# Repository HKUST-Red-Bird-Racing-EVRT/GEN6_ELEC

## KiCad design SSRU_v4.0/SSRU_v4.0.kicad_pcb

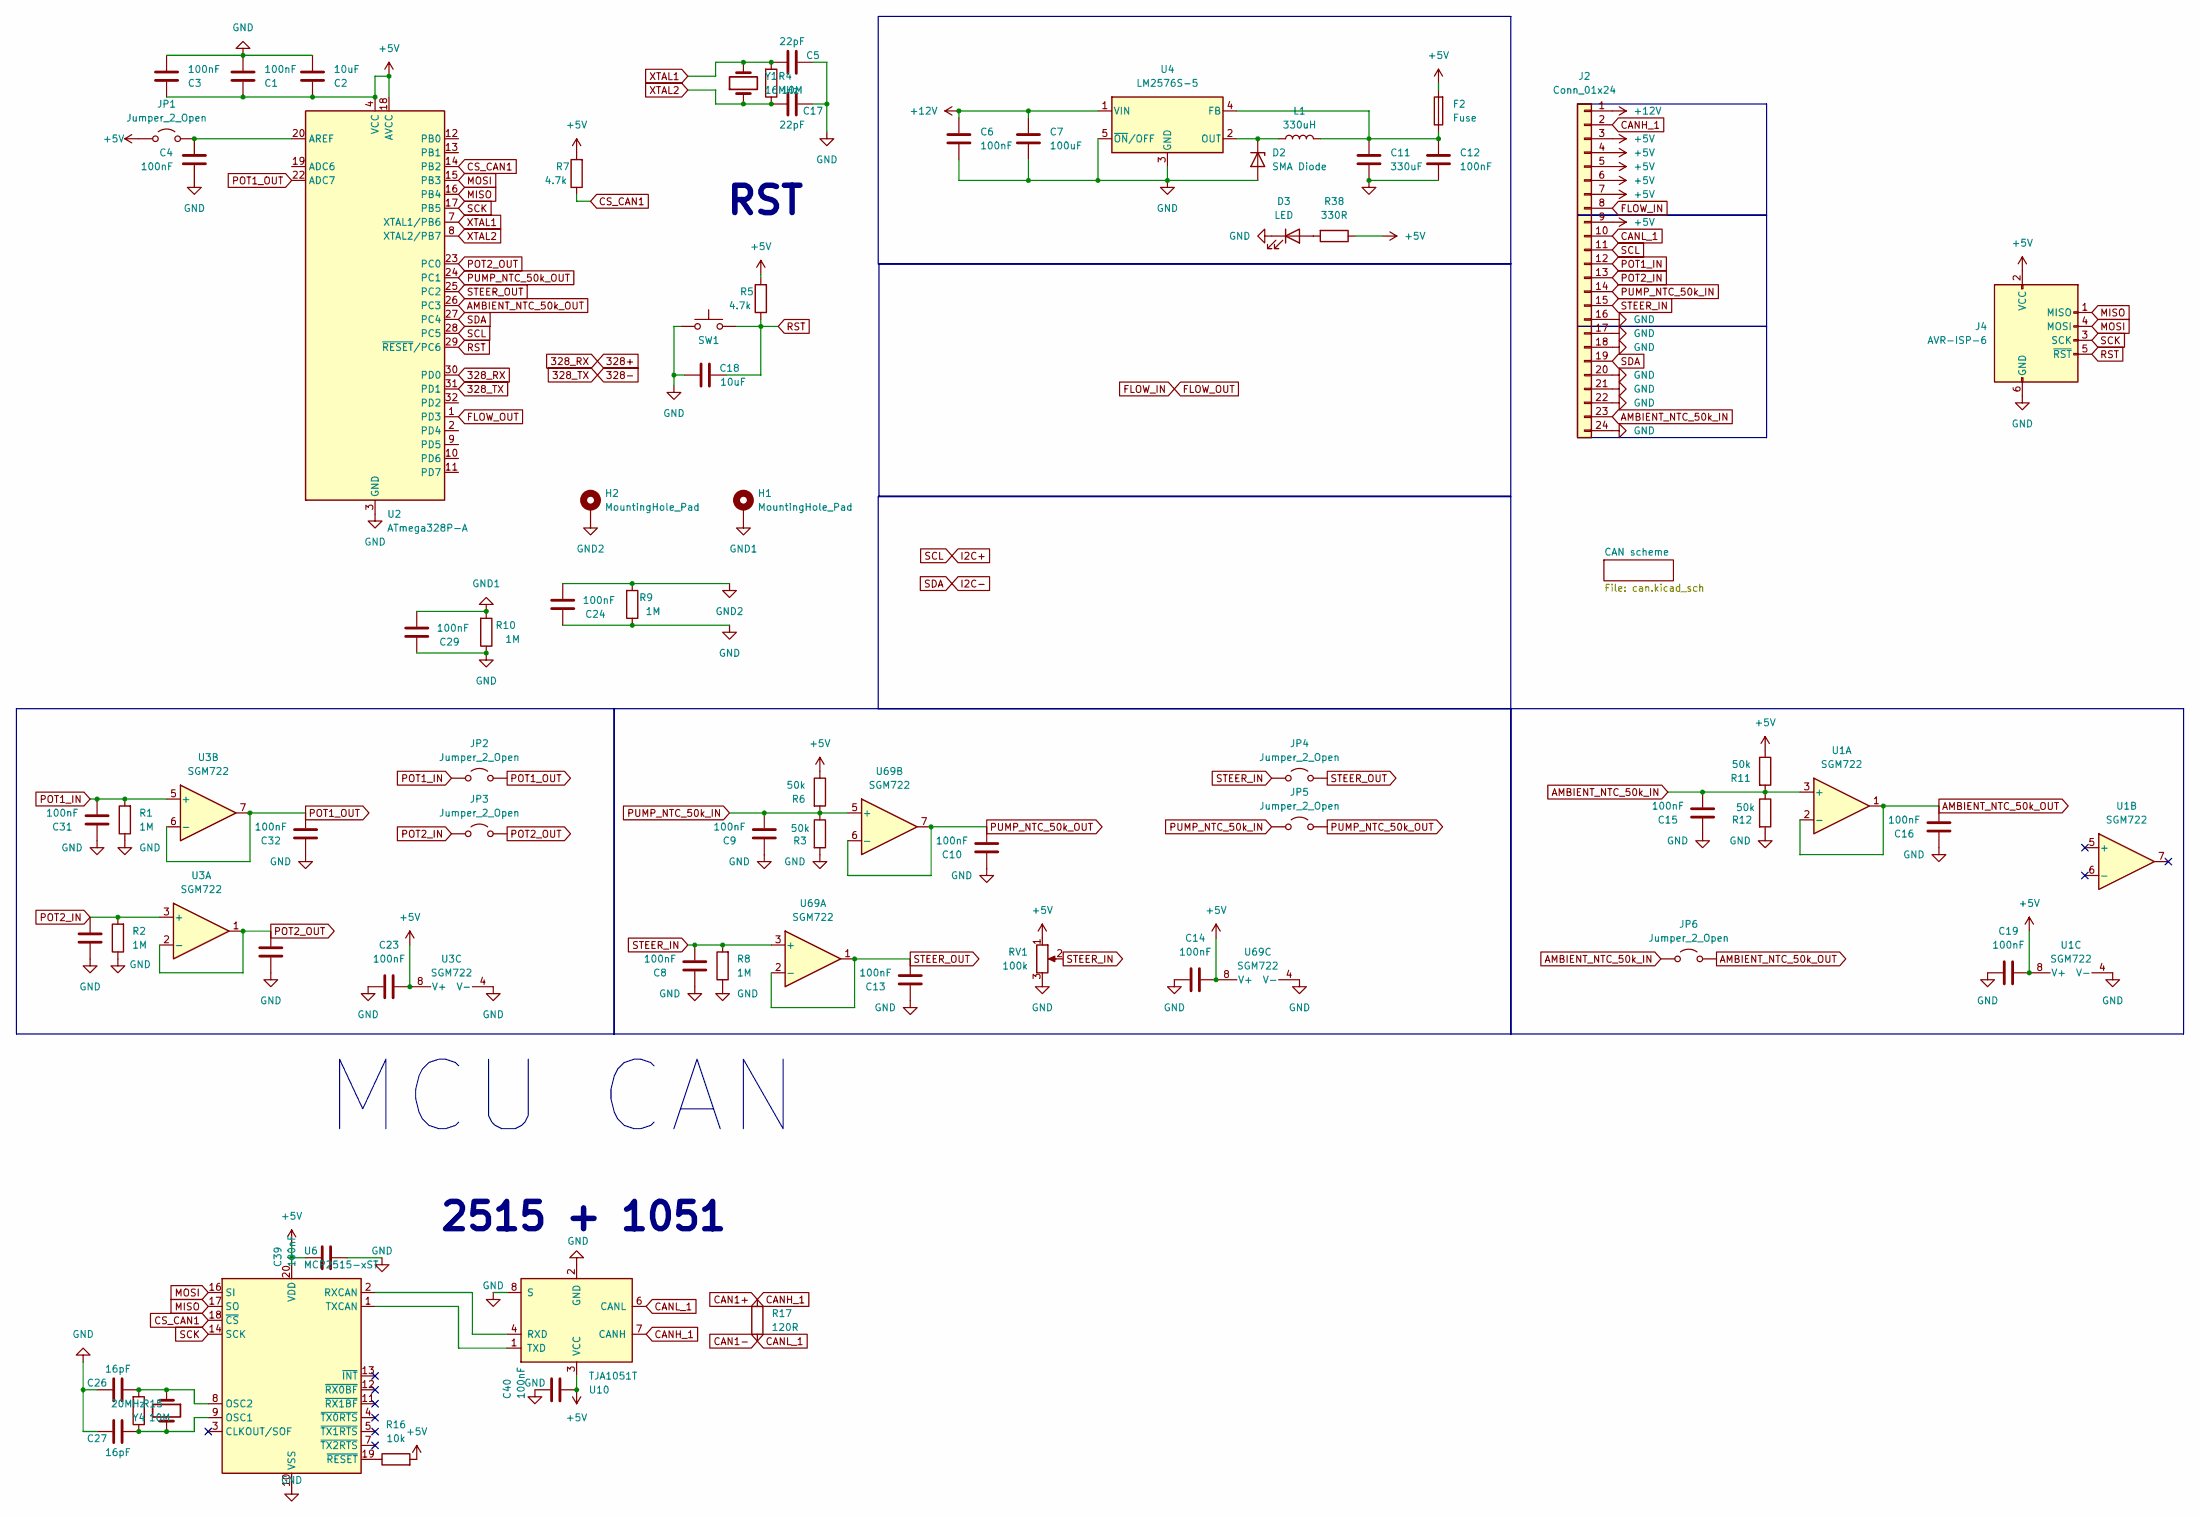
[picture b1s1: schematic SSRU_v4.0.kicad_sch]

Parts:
C1, C3, C4, C6, C8, C9, C10, C12, C13, C14, C15, C16, C19, C23, C24, C29, C31, C32, C36, C37, C39, C40: 100nF; C_0805_2012Metric_Pad1.18x1.45mm_HandSolder_L
C2, C18: 10uF; C_0805_2012Metric_Pad1.18x1.45mm_HandSolder_L
C5, C17: 22pF; C_0805_2012Metric_Pad1.18x1.45mm_HandSolder_L
C7: 100uF; CP_Radial_D6.3mm_P2.50mm_handsolder
C11: 330uF; CP_Radial_D6.3mm_P2.50mm_handsolder
C26, C27: 16pF; C_0805_2012Metric_Pad1.18x1.45mm_HandSolder_L
D2: SMA Diode; D_SMA_Handsoldering
D3: LED; LED_0805_2012Metric_Pad1.45x1.40mm_HandSolder
F2: Fuse; Fuse_1210_3225Metric_Pad1.42x2.65mm_HandSolder
H1, H2: MountingHole_Pad; MountingHole_3.2mm_M3_ISO14580_Pad
J2: Conn_01x24; HD241_24pin
J4: AVR-ISP-6; PinHeader_2x03_P2.54mm_Vertical
JP1, JP2, JP3, JP4, JP5, JP6: Jumper_2_Open; SolderJumper-2_P1.3mm_Open_Pad1.0x1.5mm
L1: 330uH; L_10.4x10.4_H4.8
R1, R2, R8, R9, R10: 1M; R_0805_2012Metric_Pad1.20x1.40mm_HandSolder_L
R3, R6, R11, R12: 50k; R_0805_2012Metric_Pad1.20x1.40mm_HandSolder_L
R4, R15: 10M; R_0805_2012Metric_Pad1.20x1.40mm_HandSolder_L
R5, R7: 4.7k; R_0805_2012Metric_Pad1.20x1.40mm_HandSolder_L
R16: 10k; R_0805_2012Metric_Pad1.20x1.40mm_HandSolder_L
R17: 120R; R_0805_2012Metric_Pad1.20x1.40mm_HandSolder_L
R38: 330R; R_0805_2012Metric_Pad1.20x1.40mm_HandSolder_L
RV1: 100k
SW1: SW_Push; SW_PUSH_6mm_H5mm
U1, U3, U69: SGM722; SOIC-8_3.9x4.9mm_P1.27mm_RMC_Handsolder
U2: ATmega328P-A; TQFP-32_7x7mm_P0.8mm_L
U4: LM2576S-5; TO-263-5_TabPin3_Handsolder
U6: MCP2515-xST; TSSOP-20_4.4x6.5mm_P0.65mm
U10: TJA1051T; SOIC-8_3.9x4.9mm_P1.27mm_RMC_Handsolder
Y1: 16MHz; Crystal_HC49-U_Vertical_W_SMD
Y4: 20MHz; Crystal_HC49-U_Vertical_W_SMD

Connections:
328+: U2.30 (PD0)
328-: U2.31 (PD1)
+5V: C1.2, C2.2, C3.2, C14.2, C19.2, C23.2, C39.2, C40.1, F2.2, J2.3, J2.4, J2.5, J2.6, J2.7, J2.9, J4.2 (VCC), JP1.1 (A), R5.2, R6.1, R7.2, R11.1, R16.2, R38.1, RV1.1, U1.8 (V+), U2.4 (VCC), U2.6 (VCC), U2.18 (AVCC), U3.8 (V+), U6.20 (VDD), U10.3 (VCC), U69.8 (V+)
+12V: C6.2, C7.1, J2.1, U4.1 (VIN)
AMBIENT_NTC_50k_IN: C15.2, J2.23, JP6.1 (A), R11.2, R12.1, U1.3 (+)
AMBIENT_NTC_50k_OUT: C16.2, JP6.2 (B), U1.1, U1.2 (-), U2.26 (PC3)
CAN1+: J2.2, R17.2, U10.7 (CANH)
CAN1-: J2.10, R17.1, U10.6 (CANL)
CS_CAN1: R7.1, U2.14 (PB2), U6.18 (~CS)
FLOW_IN: J2.8, U2.1 (PD3)
GND: C1.1, C2.1, C3.1, C4.1, C5.1, C6.1, C7.2, C8.1, C9.1, C10.1, C11.2, C12.1, C13.1, C14.1, C15.1, C16.1, C17.1, C18.1, C19.1, C23.1, C24.1, C26.1, C27.1, C29.1, C31.1, C32.1, C36.1, C37.1, C39.1, C40.2, D2.2 (A), D3.1 (K), J2.16, J2.17, J2.18, J2.20, J2.21, J2.22, J2.24, J4.6 (GND), R1.1, R2.1, R3.2, R8.1, R9.1, R10.1, R12.2, RV1.3, SW1.1, U1.4 (V-), U2.3 (GND), U2.5 (GND), U2.21 (GND), U3.4 (V-), U4.3 (GND), U4.5 (~ON/OFF), U6.10 (VSS), U10.2 (GND), U10.8 (S), U69.4 (V-)
GND1: C29.2, H1.1, R10.2
GND2: C24.2, H2.1, R9.2
I2C+: J2.11, U2.28 (PC5)
I2C-: J2.19, U2.27 (PC4)
MISO: J4.1 (MISO), U2.16 (PB4), U6.17 (SO)
MOSI: J4.4 (MOSI), U2.15 (PB3), U6.16 (SI)
unnamed: D2.1 (K), L1.1, U4.2 (OUT)
unnamed: D3.2 (A), R38.2
unnamed: C4.2, JP1.2 (B), U2.20 (AREF)
unnamed: C11.1, C12.2, F2.1, L1.2, U4.4 (FB)
unnamed: C27.2, R15.1, U6.9 (OSC1), Y4.2
unnamed: C26.2, R15.2, U6.8 (OSC2), Y4.1
unnamed: R16.1, U6.19 (~RESET)
unnamed: U6.2 (RXCAN), U10.4 (RXD)
unnamed: U6.1 (TXCAN), U10.1 (TXD)
POT1_IN: C31.2, J2.12, JP2.1 (A), R1.2, U3.5 (+)
POT1_OUT: C32.2, JP2.2 (B), U2.22 (ADC7), U3.6 (-), U3.7
POT2_IN: C36.2, J2.13, JP3.1 (A), R2.2, U3.3 (+)
POT2_OUT: C37.2, JP3.2 (B), U2.23 (PC0), U3.1, U3.2 (-)
PUMP_NTC_50k_IN: C9.2, J2.14, JP5.1 (A), R3.1, R6.2, U69.5 (+)
PUMP_NTC_50k_OUT: C10.2, JP5.2 (B), U2.24 (PC1), U69.6 (-), U69.7
RST: C18.2, J4.5 (~RST), R5.1, SW1.2, U2.29 (~RESET/PC6)
SCK: J4.3 (SCK), U2.17 (PB5), U6.14 (SCK)
STEER_IN: C8.2, J2.15, JP4.1 (A), R8.2, RV1.2, U69.3 (+)
STEER_OUT: C13.2, JP4.2 (B), U2.25 (PC2), U69.1, U69.2 (-)
XTAL1: C5.2, R4.2, U2.7 (XTAL1/PB6), Y1.2
XTAL2: C17.2, R4.1, U2.8 (XTAL2/PB7), Y1.1

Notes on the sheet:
MCU CAN
2515 + 1051
RST

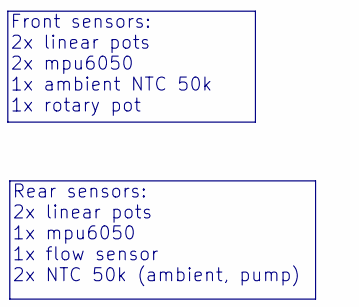
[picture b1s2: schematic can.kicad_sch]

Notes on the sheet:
Front sensors: 2x linear pots 2x mpu6050 1x ambient NTC 50k 1x rotary pot
Rear sensors: 2x linear pots 1x mpu6050 1x flow sensor 2x NTC 50k (ambient, pump)

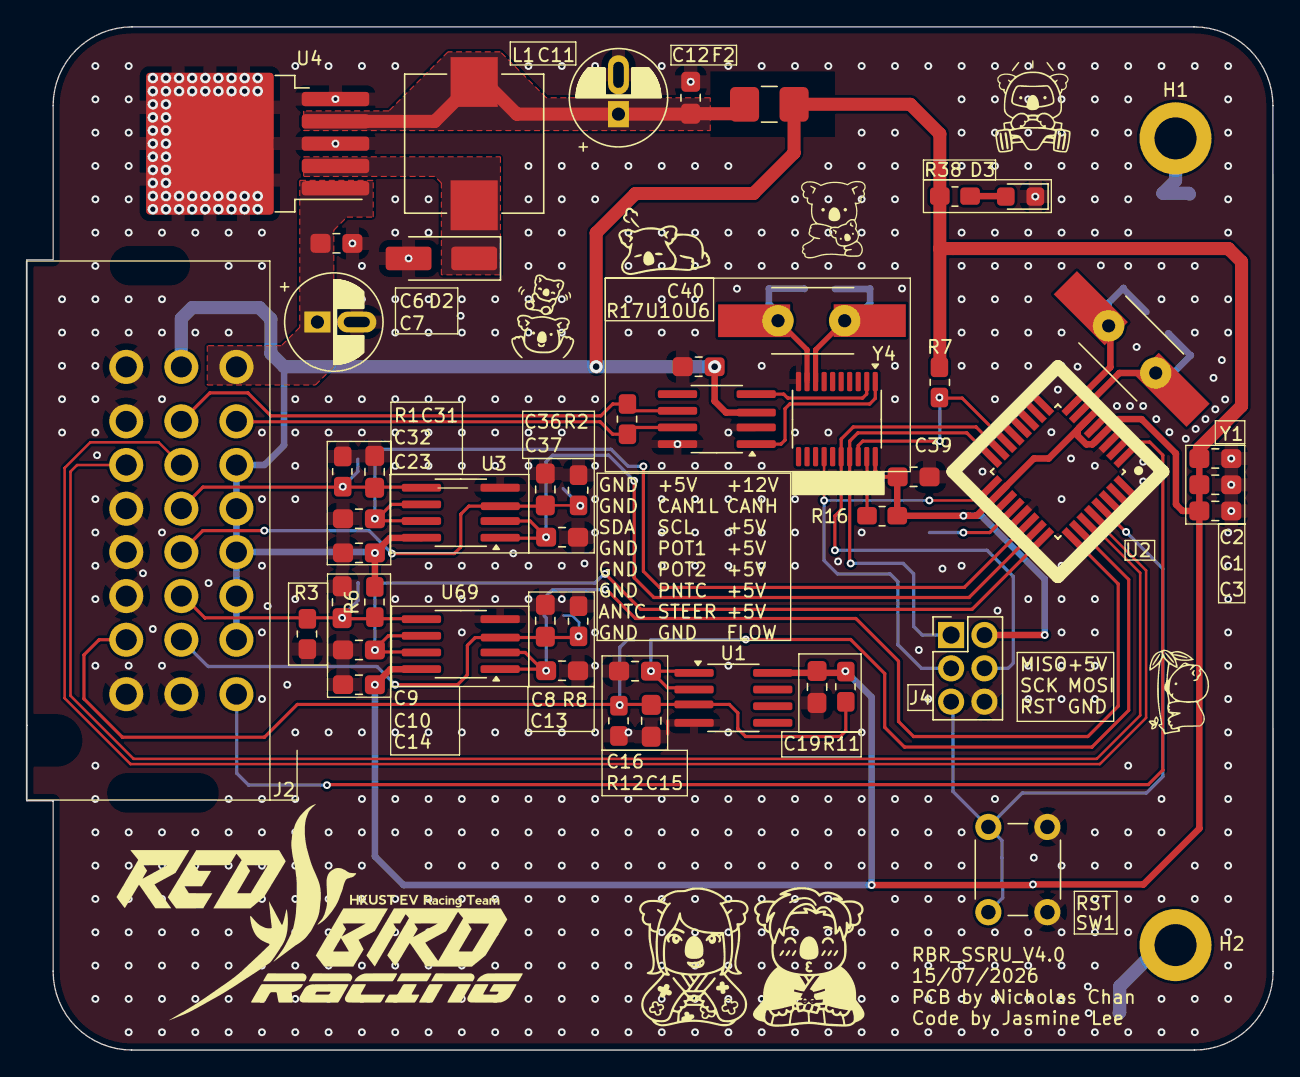
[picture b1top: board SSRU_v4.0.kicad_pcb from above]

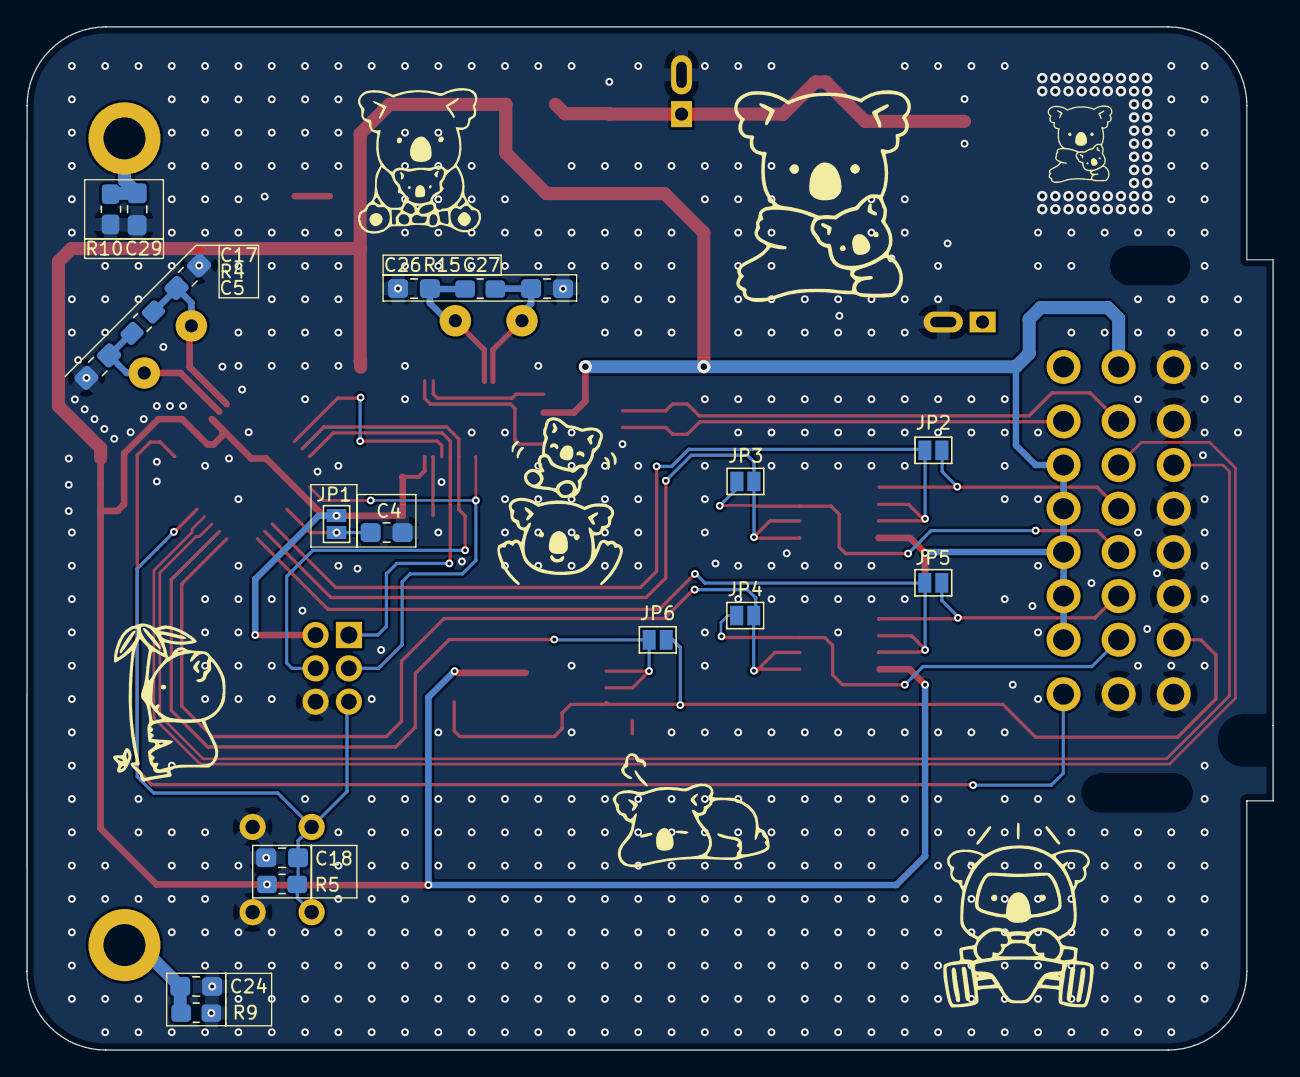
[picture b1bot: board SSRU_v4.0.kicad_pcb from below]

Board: 2 copper layers, 95.0 x 78.0 mm, 70 parts (19 on the bottom side), 36 nets.

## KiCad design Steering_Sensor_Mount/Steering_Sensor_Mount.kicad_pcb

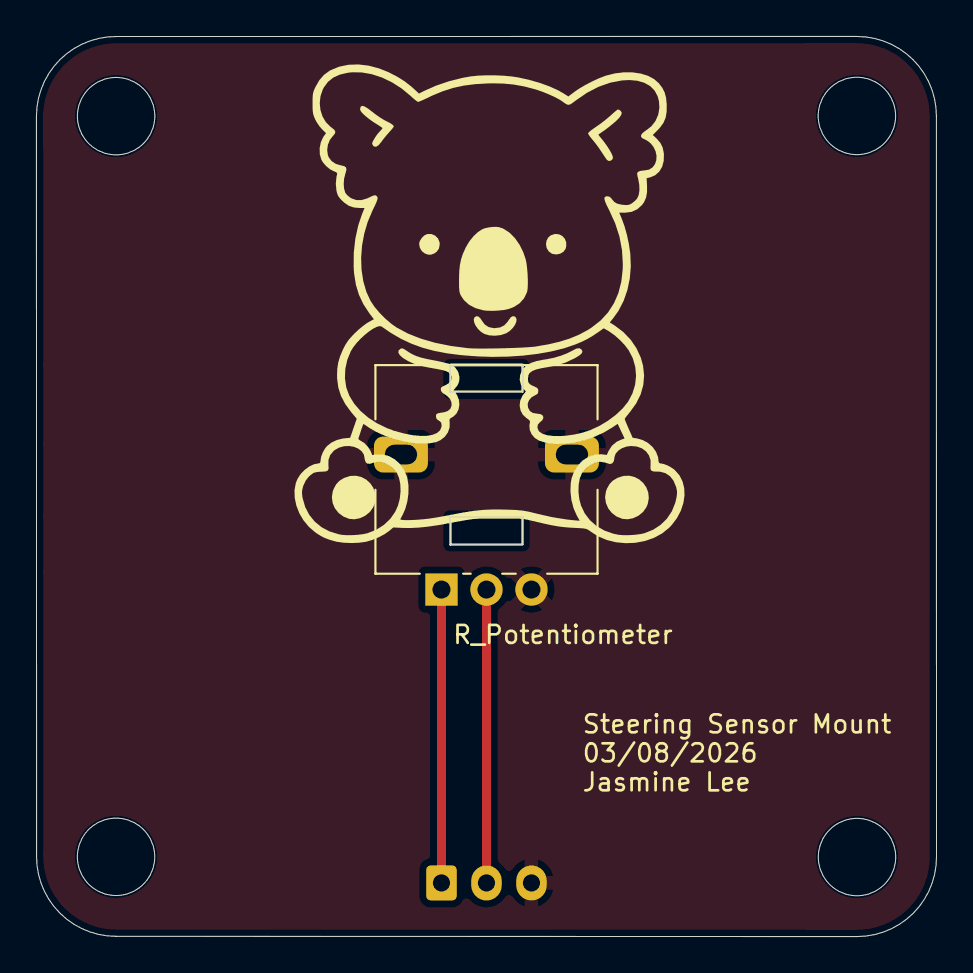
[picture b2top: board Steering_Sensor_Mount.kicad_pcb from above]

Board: 2 copper layers, 50.0 x 50.0 mm, 6 parts (1 on the bottom side), 3 nets.

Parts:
H1, H2, H3, H4: MountingHole; MountingHole_4.3mm_M4
J1: Conn_01x03; JST_XH_B3B-XH-A_1x03_P2.50mm_Vertical
RV1: R_Potentiometer; Potentiometer_Alps_RK09L_Single_Vertical

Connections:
+5V: J1.1, RV1.1
GND: J1.3, RV1.3, RV1.MP (MountPin)
unnamed: J1.2, RV1.2

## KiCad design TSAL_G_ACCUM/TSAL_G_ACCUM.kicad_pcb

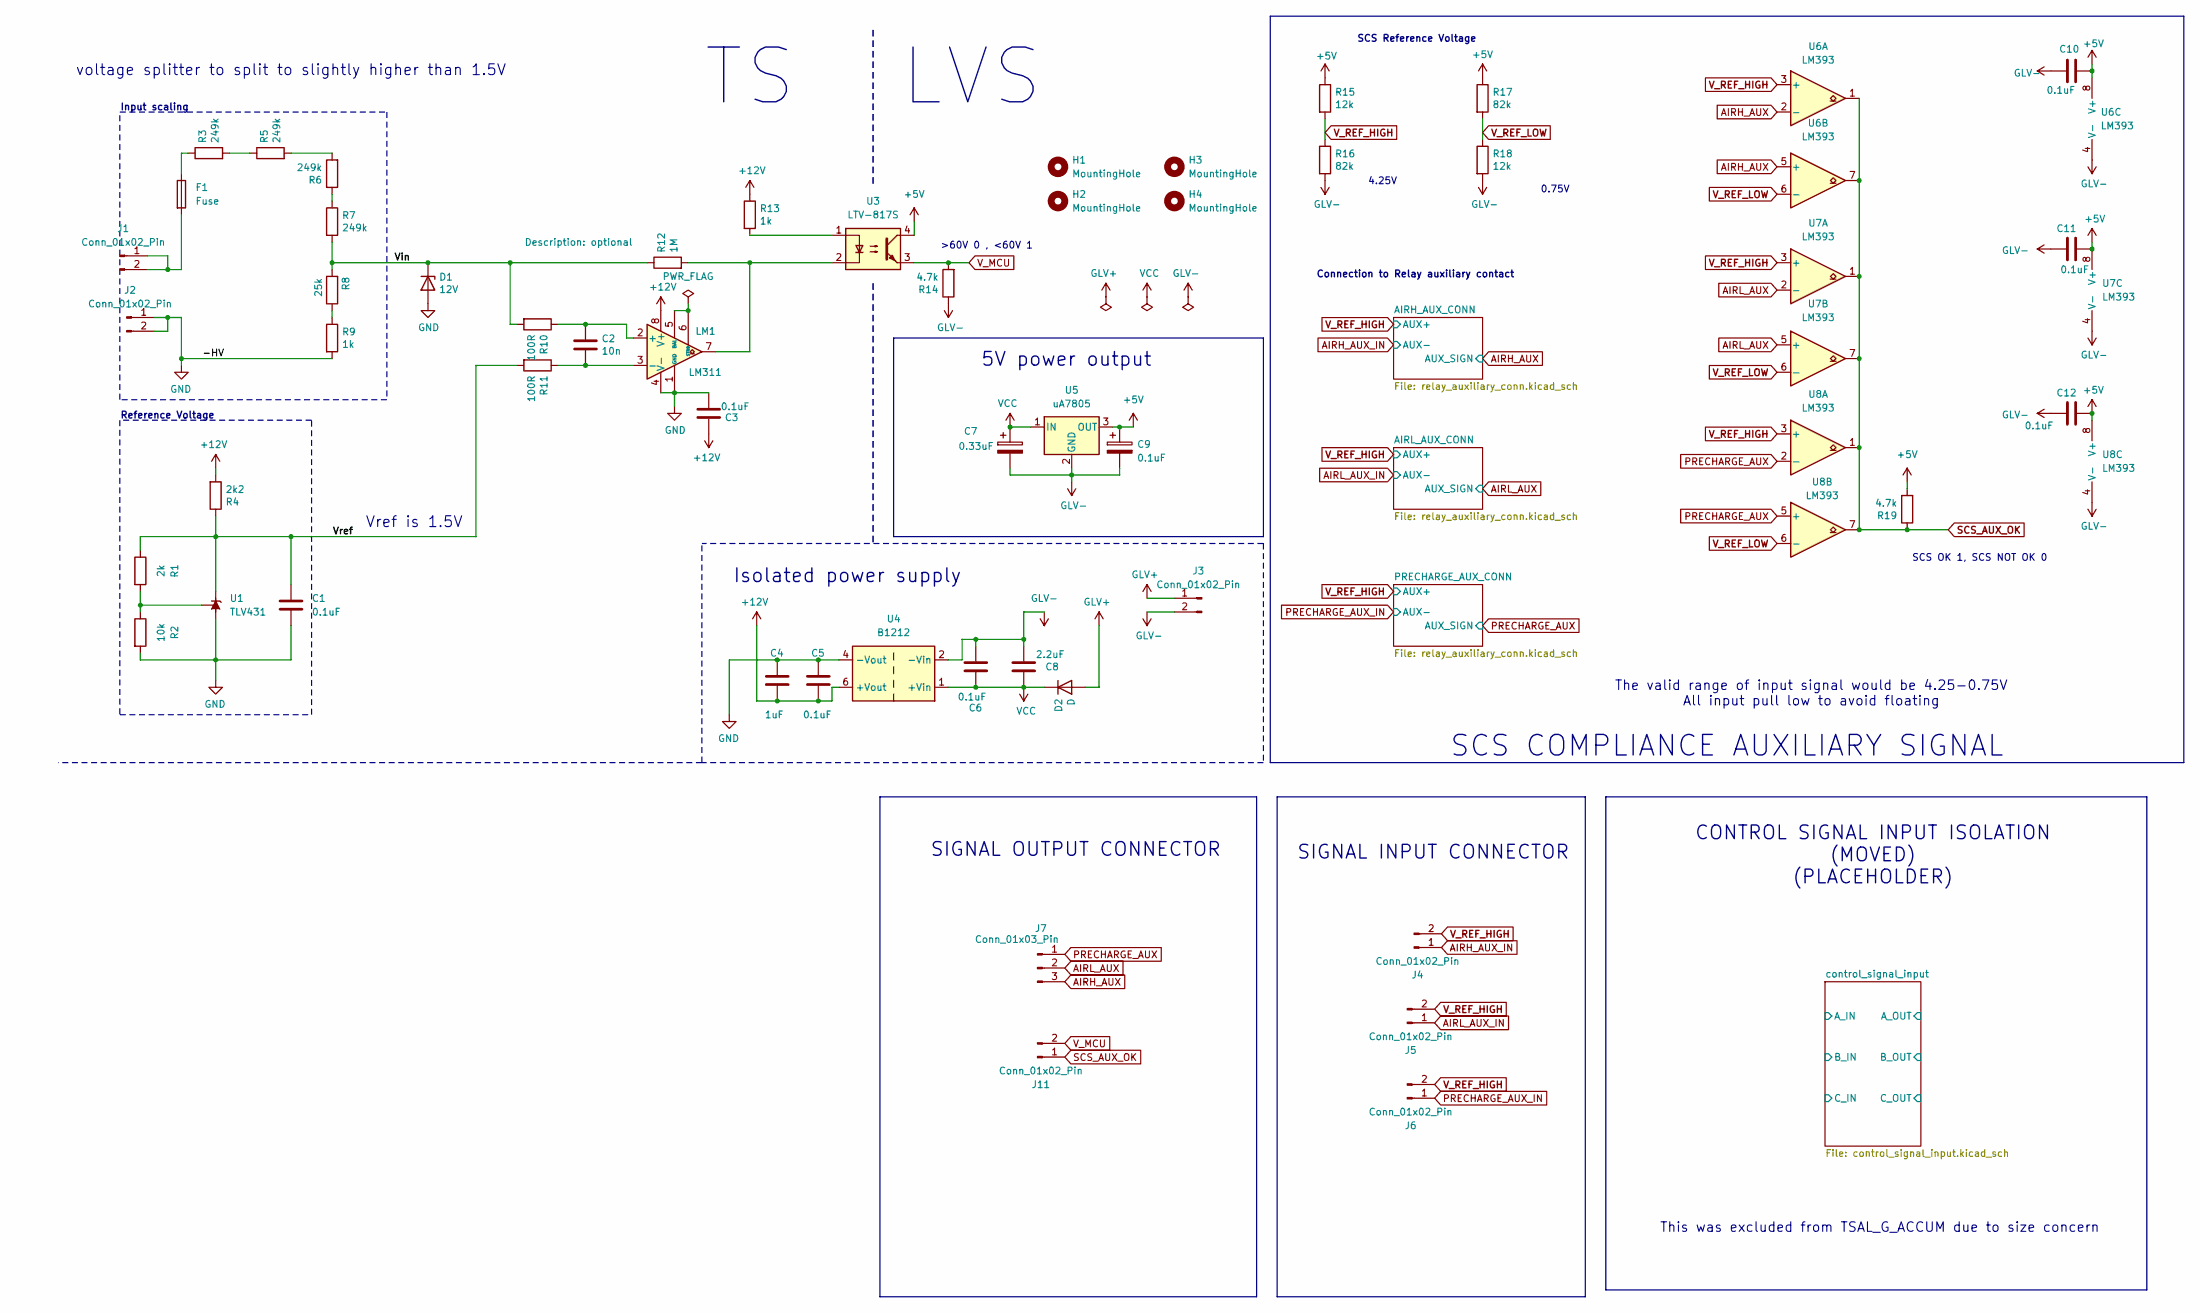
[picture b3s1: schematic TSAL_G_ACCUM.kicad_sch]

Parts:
C1, C3, C5, C6, C9, C10, C11, C12: 0.1uF; C_0805_2012Metric_Pad1.18x1.45mm_HandSolder_L
C2: 10n; C_0805_2012Metric_Pad1.18x1.45mm_HandSolder_L
C4: 1uF; C_0805_2012Metric_Pad1.18x1.45mm_HandSolder_L
C7: 0.33uF; C_0805_2012Metric_Pad1.18x1.45mm_HandSolder_L
C8: 2.2uF; C_0805_2012Metric_Pad1.18x1.45mm_HandSolder_L
D1: 12V; D_DO-35_SOD27_P7.62mm_Horizontal
D2: D; D_SMA_Handsoldering
F1: Fuse; Fuse_Littelfuse-NANO2-885
H1, H2, H3, H4: MountingHole; MountingHole_4.3mm_M4
J1, J2, J3, J4, J5, J6, J11: Conn_01x02_Pin; Molex_Micro-Fit_3.0_43650-0200_1x02_P3.00mm_Horizontal
J7: Conn_01x03_Pin; Molex_Micro-Fit_3.0_43650-0300_1x03_P3.00mm_Horizontal
LM1: LM311; SOIC-8_3.9x4.9mm_P1.27mm_RMC_Handsolder
R1: 2k; R_0805_2012Metric_Pad1.20x1.40mm_HandSolder_L
R2: 10k; R_0805_2012Metric_Pad1.20x1.40mm_HandSolder_L
R3, R5, R6, R7: 249k; R_0805_2012Metric_Pad1.20x1.40mm_HandSolder_L
R4: 2k2; R_0805_2012Metric_Pad1.20x1.40mm_HandSolder_L
R8: 25k; R_0805_2012Metric_Pad1.20x1.40mm_HandSolder_L
R9, R13: 1k; R_0805_2012Metric_Pad1.20x1.40mm_HandSolder_L
R10, R11: 100R; R_0805_2012Metric_Pad1.20x1.40mm_HandSolder_L
R12: 1M; R_0805_2012Metric_Pad1.20x1.40mm_HandSolder_L
R14, R19: 4.7k; R_0805_2012Metric_Pad1.20x1.40mm_HandSolder_L
R15, R18: 12k; R_0805_2012Metric_Pad1.20x1.40mm_HandSolder_L
R16, R17: 82k; R_0805_2012Metric_Pad1.20x1.40mm_HandSolder_L
U1: TLV431; SOT-23
U3: LTV-817S; SMDIP-4_W9.53mm
U4: B1212; Converter_DCDC_F1212
U5: uA7805; TO-252-2
U6, U7, U8: LM393; SOIC-8_3.9x4.9mm_P1.27mm_RMC_Handsolder

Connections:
+5V: C9.1, C10.2, C11.2, C12.2, R15.1, R17.1, R19.2, U3.4, U5.3 (OUT), U6.8 (V+), U7.8 (V+), U8.8 (V+)
+12V: C3.1, C4.2, C5.2, LM1.8 (V+), R4.2, R13.1, U4.6 (+Vout)
/Vin: D1.1 (K), R7.2, R8.2, R10.2, R12.1
/Vref: C1.1, R1.1, R4.1, R11.2, U1.2 (K)
AIRH_AUX: J7.3, U6.2 (-), U6.5 (+); also elsewhere on the board
AIRH_AUX_IN: J4.1; also elsewhere on the board
AIRL_AUX: J7.2, U7.2 (-), U7.5 (+); also elsewhere on the board
AIRL_AUX_IN: J5.1; also elsewhere on the board
GLV+: D2.2 (A), J3.1
GLV-: C6.1, C7.2, C8.1, C9.2, C10.1, C11.1, C12.1, J3.2, R14.1, R16.2, R18.2, U4.2 (-Vin), U5.2 (GND), U6.4 (V-), U7.4 (V-), U8.4 (V-)
GND: C1.2, C3.2, C4.1, C5.1, D1.2 (A), J2.1, J2.2, LM1.1 (GND), LM1.4 (V-), R2.2, R9.2, U1.3 (A), U4.4 (-Vout)
unnamed: F1.1, R3.1
unnamed: F1.2, J1.1, J1.2
unnamed: C2.1, LM1.2 (+), R10.1
unnamed: C2.2, LM1.3 (-), R11.1
unnamed: LM1.5 (BAL), LM1.6 (STRB)
unnamed: LM1.7, R12.2, U3.2
unnamed: R3.2, R5.1
unnamed: R5.2, R6.2
unnamed: R6.1, R7.1
unnamed: R8.1, R9.1
unnamed: R13.2, U3.1
unnamed: R1.2, R2.1, U1.1 (REF)
PRECHARGE_AUX: J7.1, U8.2 (-), U8.5 (+); also elsewhere on the board
PRECHARGE_AUX_IN: J6.1; also elsewhere on the board
SCS_AUX_OK: J11.1, R19.1, U6.1, U6.7, U7.1, U7.7, U8.1, U8.7
VCC: C6.2, C7.1, C8.2, D2.1 (K), U4.1 (+Vin), U5.1 (IN)
V_MCU: J11.2, R14.2, U3.3
V_REF_HIGH: J4.2, J5.2, J6.2, R15.2, R16.1, U6.3 (+), U7.3 (+), U8.3 (+)
V_REF_LOW: R17.2, R18.1, U6.6 (-), U7.6 (-), U8.6 (-); also elsewhere on the board

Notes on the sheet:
SCS OK 1, SCS NOT OK 0
SIGNAL OUTPUT CONNECTOR
voltage splitter to split to slightly higher than 1.5V
SCS Reference Voltage
4.25V
>60V 0 , <60V 1
This was excluded from TSAL_G_ACCUM due to size concern
Input scaling
Isolated power supply
0.75V
5V power output
LVS
Reference Voltage
Connection to Relay auxiliary contact
Vref is 1.5V
SIGNAL INPUT CONNECTOR
The valid range of input signal would be 4.25-0.75V All input pull low to avoid floating
CONTROL SIGNAL INPUT ISOLATION (MOVED) (PLACEHOLDER)
SCS COMPLIANCE AUXILIARY SIGNAL

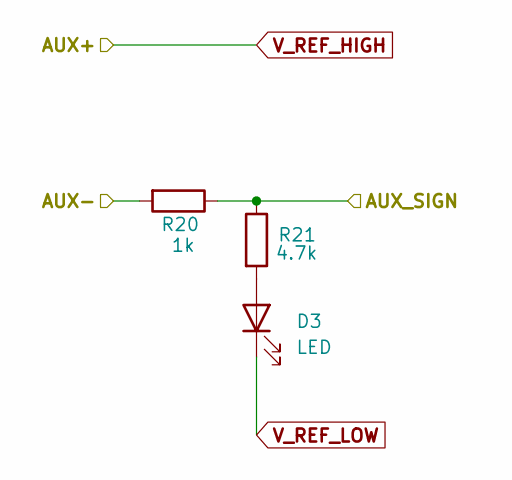
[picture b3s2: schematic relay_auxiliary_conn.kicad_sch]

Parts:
D3: LED; LED_0805_2012Metric_Pad1.45x1.40mm_HandSolder
R20: 1k; R_0805_2012Metric_Pad1.20x1.40mm_HandSolder_L
R21: 4.7k; R_0805_2012Metric_Pad1.20x1.40mm_HandSolder_L

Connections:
AIRH_AUX: R20.1, R21.1; also elsewhere on the board
AIRH_AUX_IN: R20.2; also elsewhere on the board
unnamed: D3.2 (A), R21.2
V_REF_LOW: D3.1 (K); also elsewhere on the board

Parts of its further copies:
D4, D5: LED; LED_0805_2012Metric_Pad1.45x1.40mm_HandSolder
R22, R24: 1k; R_0805_2012Metric_Pad1.20x1.40mm_HandSolder_L
R23, R25: 4.7k; R_0805_2012Metric_Pad1.20x1.40mm_HandSolder_L

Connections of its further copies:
AIRL_AUX: R22.1, R23.1; also elsewhere on the board
AIRL_AUX_IN: R22.2; also elsewhere on the board
unnamed: D4.2 (A), R23.2
unnamed: D5.2 (A), R25.2
PRECHARGE_AUX: R24.1, R25.1; also elsewhere on the board
PRECHARGE_AUX_IN: R24.2; also elsewhere on the board
V_REF_LOW: D4.1 (K), D5.1 (K); also elsewhere on the board

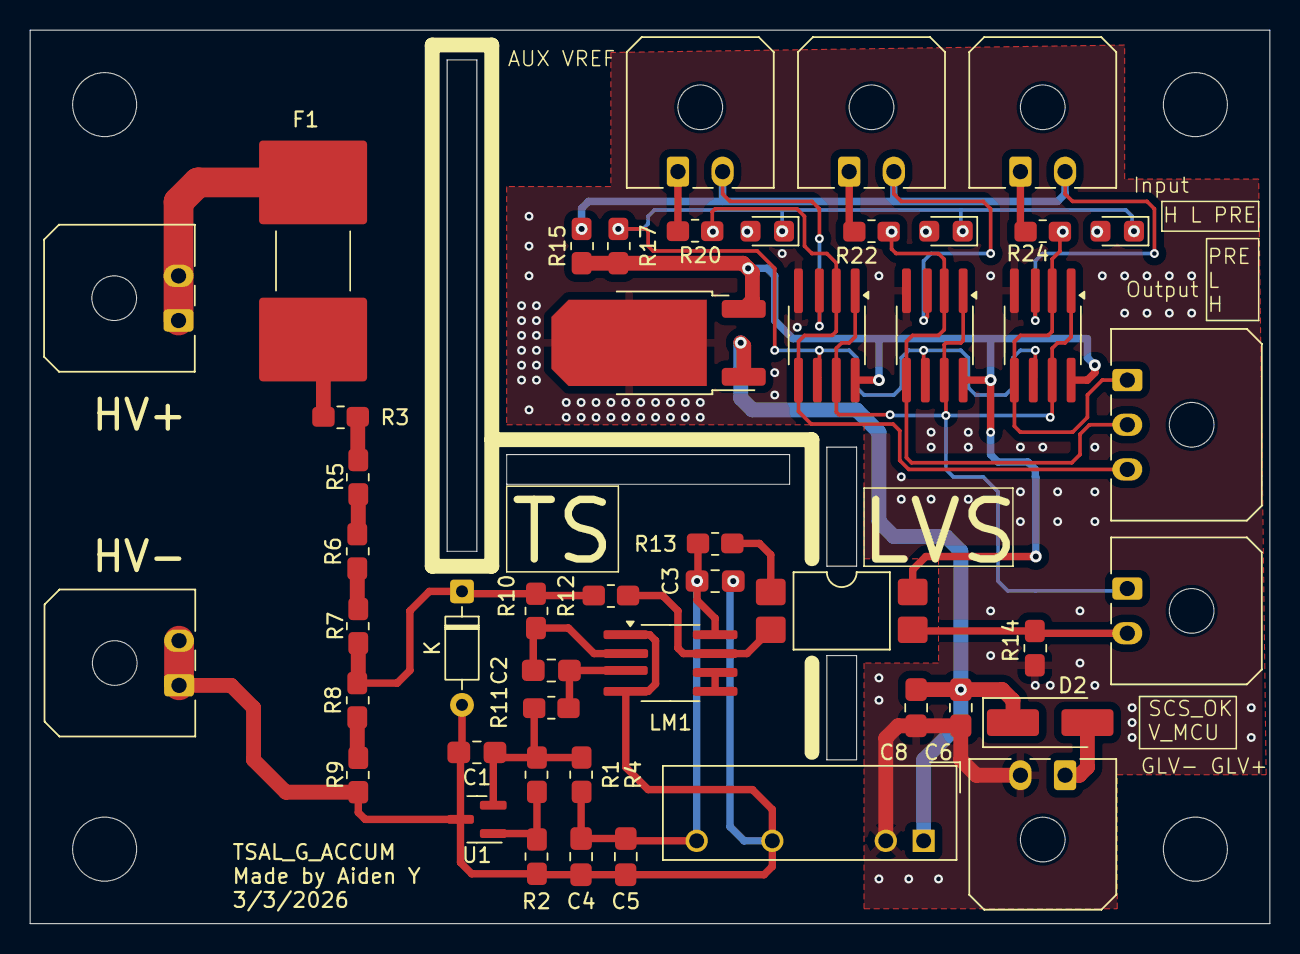
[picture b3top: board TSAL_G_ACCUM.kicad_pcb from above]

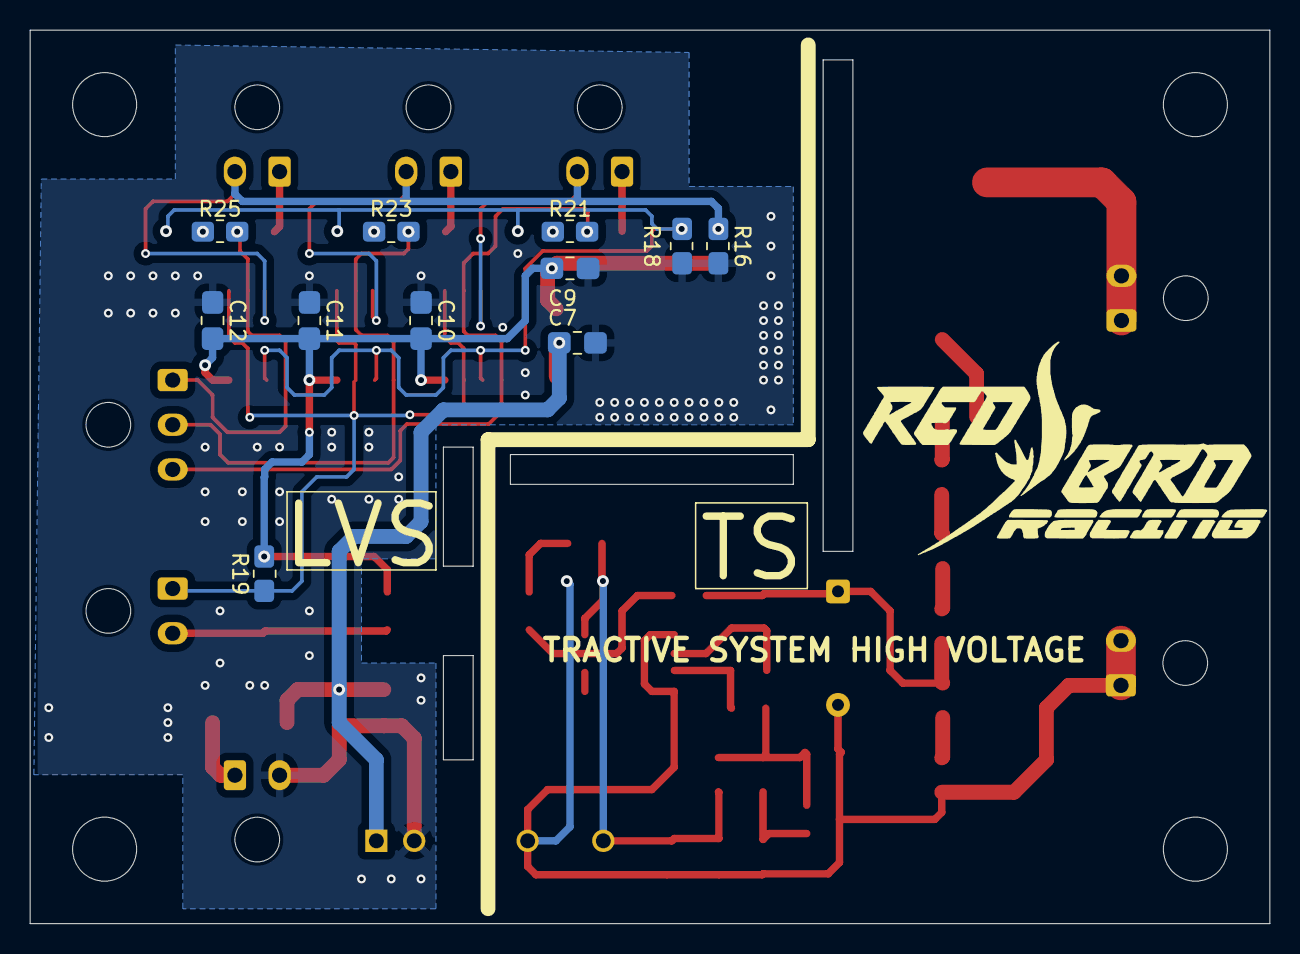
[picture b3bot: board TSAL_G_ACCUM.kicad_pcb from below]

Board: 2 copper layers, 83.2 x 60.0 mm, 63 parts (11 on the bottom side), 33 nets.

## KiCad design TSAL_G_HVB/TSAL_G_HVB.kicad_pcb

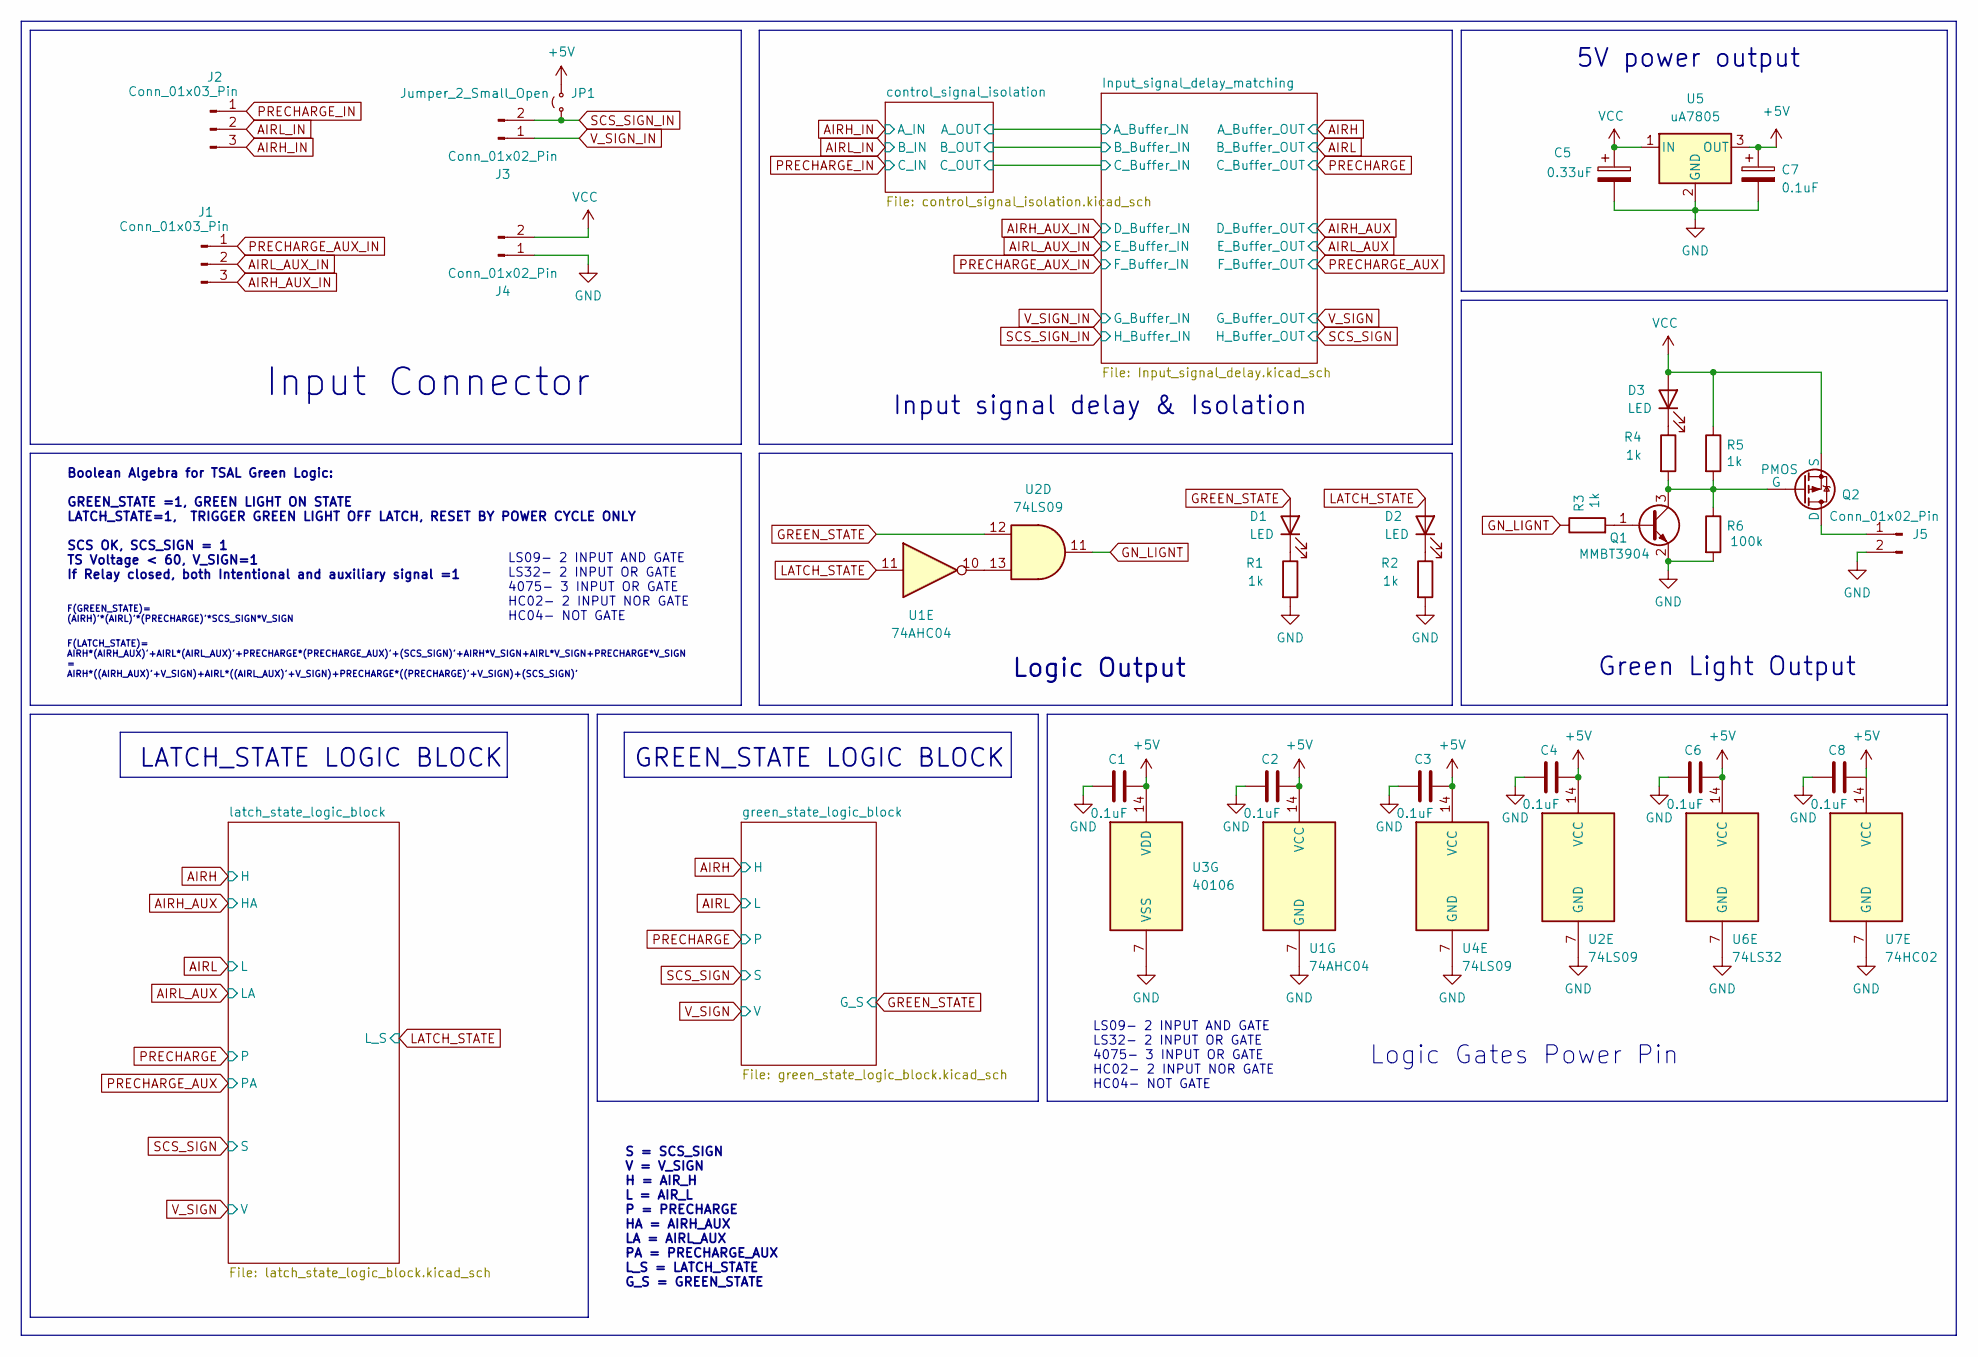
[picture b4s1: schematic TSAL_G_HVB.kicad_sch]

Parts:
C1, C2, C3, C4, C6, C8: 0.1uF; C_0805_2012Metric_Pad1.18x1.45mm_HandSolder_L
C5: 0.33uF; CP_Radial_D5.0mm_P2.50mm
C7: 0.1uF; CP_Radial_D5.0mm_P2.50mm
D1, D2, D3: LED; LED_0805_2012Metric_Pad1.45x1.40mm_HandSolder
J1, J2: Conn_01x03_Pin; Molex_Micro-Fit_3.0_43650-0300_1x03_P3.00mm_Horizontal
J3, J4, J5: Conn_01x02_Pin; Molex_Micro-Fit_3.0_43650-0200_1x02_P3.00mm_Horizontal
JP1: Jumper_2_Small_Open; SolderJumper-2_P1.3mm_Open_Pad1.0x1.5mm
Q1: MMBT3904; SOT-23
Q2: PMOS; TO-252-2
R1, R2, R3, R4, R5: 1k; R_0805_2012Metric_Pad1.20x1.40mm_HandSolder_L
R6: 100k; R_0805_2012Metric_Pad1.20x1.40mm_HandSolder_L
U1: 74AHC04; SOIC127P600X175-14N
U2, U4: 74LS09; SOIC127P600X175-14N
U3: 40106; SOIC127P600X175-14N
U5: uA7805; TO-252-2
U6: 74LS32; SOIC127P600X175-14N
U7: 74HC02; SOIC127P600X175-14N

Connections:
+5V: C1.2, C2.2, C3.2, C4.2, C6.2, C7.1, C8.2, JP1.2 (B), U1.14 (VCC), U2.14 (VCC), U3.14 (VDD), U4.14 (VCC), U5.3 (OUT), U6.14 (VCC), U7.14 (VCC); also elsewhere on the board
AIRH_AUX: J1.3; also elsewhere on the board
AIRH_IN: J2.3; also elsewhere on the board
AIRL_AUX: J1.2; also elsewhere on the board
AIRL_IN: J2.2; also elsewhere on the board
GND: C1.1, C2.1, C3.1, C4.1, C5.2, C6.1, C7.2, C8.1, J4.1, J5.2, Q1.2 (E), R1.2, R2.2, R6.2, U1.7 (GND), U2.7 (GND), U3.7 (VSS), U4.7 (GND), U5.2 (GND), U6.7 (GND), U7.7 (GND); also elsewhere on the board
GN_LIGNT: R3.1, U2.11
GREEN_STATE: D1.2 (A), U2.12; also elsewhere on the board
LATCH_STATE: D2.2 (A), U1.11; also elsewhere on the board
unnamed: D1.1 (K), R1.1
unnamed: D2.1 (K), R2.1
unnamed: D3.1 (K), R4.1
unnamed: J5.1, Q2.1 (D)
unnamed: Q1.1 (B), R3.2
unnamed: Q1.3 (C), Q2.2 (G), R4.2, R5.2, R6.1
unnamed: U1.10, U2.13
PRECHARGE_AUX: J1.1; also elsewhere on the board
PRECHARGE_IN: J2.1; also elsewhere on the board
SCS_SIGN_IN: J3.2, JP1.1 (A); also elsewhere on the board
VCC: C5.1, D3.2 (A), J4.2, Q2.3 (S), R5.1, U5.1 (IN); also elsewhere on the board
V_SIGN: J3.1; also elsewhere on the board

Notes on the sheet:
S = SCS_SIGN V = V_SIGN H = AIR_H L = AIR_L P = PRECHARGE HA = AIRH_AUX LA = AIRL_AUX PA = PRECHARGE_AUX L_S = LATCH_STATE G_S = GREEN_STATE
Boolean Algebra for TSAL Green Logic: GREEN_STATE =1, GREEN LIGHT ON STATE LATCH_STATE=1, TRIGGER GREEN LIGHT OFF LATCH, RESET BY POWER CYCLE ONLY SCS OK, SCS_SIGN = 1 TS Voltage < 60, V_SIGN=1 If Relay closed, both Intentional and auxiliary signal =1
5V power output
Input signal delay & Isolation
GREEN_STATE LOGIC BLOCK
F(GREEN_STATE)= (AIRH)'*(AIRL)'*(PRECHARGE)'*SCS_SIGN*V_SIGN
F(LATCH_STATE)= AIRH*(AIRH_AUX)'+AIRL*(AIRL_AUX)'+PRECHARGE*(PRECHARGE_AUX)'+(SCS_SIGN)'+AIRH*V_SIGN+AIRL*V_SIGN+PRECHARGE*V_SIGN = AIRH*((AIRH_AUX)'+V_SIGN)+AIRL*((AIRL_AUX)'+V_SIGN)+PRECHARGE*((PRECHARGE)'+V_SIGN)+(SCS_SIGN)'
Logic Gates Power Pin
Green Light Output
LS09- 2 INPUT AND GATE LS32- 2 INPUT OR GATE 4075- 3 INPUT OR GATE HC02- 2 INPUT NOR GATE HC04- NOT GATE
LATCH_STATE LOGIC BLOCK
Input Connector
Logic Output
